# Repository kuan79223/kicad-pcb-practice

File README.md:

# KiCad PCB Design Practice

Hands-on KiCad exercises covering schematic capture, component footprints, PCB layout, design-rule checks, 3D inspection, and manufacturing-file review.

> **Scope:** This repository documents learning exercises. The boards shown here have **not** been fabricated, assembled, or physically tested.

## Projects

| Project | What I practiced | Status | Details |
| --- | --- | --- | --- |
| **01 · Zener Voltage Regulator** | 12 V input / nominal 5.1 V Zener regulator; schematic, PCB routing, 3D review, DRC, Gerber/Drill inspection | PCB design exercise completed; physical verification pending | [Open project](Zener_Regulator/README.md) |
| **02 · Common-Emitter Amplifier** | 2N3904 共射極放大器、DC 偏壓、電壓增益、PCB Layout、ERC／DRC 與 Gerber 檢視 | PCB 設計完成，待實體驗證 | [Open project](CommonEmitter_Amplifier/README.md) |
| **03 · Dual-Site Power Monitoring & Fault Detection Board** | 雙通道電源監控、LTspice、TLV7031、雙層 PCB、GND Plane |理想模型模擬及 PCB 設計初版完成；實際比較器功能與實體板待驗證 | [Open project](mini-loadboard-power-monitor/README.md) |

## Project 01 · Zener Voltage Regulator

[View the full Zener Regulator design notes →](Zener_Regulator/README.md)

## Project 02 · Common-Emitter Amplifier

[View the full CommonEmitter Amplifier design notes →](CommonEmitter_Amplifier/README.md)

## Project 02 · 雙測試位置電源監控與故障偵測板

模擬兩個測試位置的供電路徑電阻差異，使用 LTspice 分析節點壓降與理想故障判斷邏輯，並在 KiCad 建立 TLV7031 比較器原理圖、雙層 PCB、測試點及背面接地銅箔平面。

模擬條件： 3.3V 供電，理想故障判斷門檻為 3.25V。

模擬結果： SITE_A 約 3.290V、SITE_B 約 3.203V，理想故障觸發臨界路徑電阻約 5.077Ω。

工程交付： LTspice 模擬、KiCad 原理圖與 PCB、ERC／DRC、BOM、Gerber 及 Drill 資料。

驗證限制： 尚未使用實際 TLV7031 SPICE 模型或實體量測驗證比較器切換門檻。

[View the full CommonEmitter Amplifier design notes →](mini-loadboard-power-monitor/README.md)

---

*Each exercise has its own README with the circuit, design images, checks, and limitations. New projects will be added to the table above.*

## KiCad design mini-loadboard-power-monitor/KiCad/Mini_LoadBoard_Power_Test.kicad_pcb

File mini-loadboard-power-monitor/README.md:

# 雙測試位置電源監控與故障偵測板

**Dual-Site Power Monitoring & Fault Detection Board**

> 專案狀態：已完成 LTspice 理想模型驗證、KiCad 原理圖、PCB 佈線及製造資料輸出；**尚未進行實體打樣、比較器實際模型驗證或電氣量測**。

## 1. 專案目的

以簡化的雙測試位置（Site A／Site B）電源路徑作為練習案例，觀察不同路徑電阻造成的電壓降，並建立低電壓故障判斷邏輯。進一步使用 KiCad 將理想判斷概念轉換為含比較器、參考電壓、測試點與雙層 PCB 的設計初版，練習從模擬、原理圖、封裝配置、PCB 佈線到製造資料整理的工程流程。

本專案是**教學與作品集用途的簡化測試電路**，不是可直接使用的商用半導體 Load Board／BIB。

## 2. 開發工具與設計內容

| 類別 | 工具／內容 |
|---|---|
| 直流及參數掃描 | LTspice（`.op`、`.step`、Behavioral Voltage Source） |
| 原理圖與 PCB | KiCad 10.0 |
| 設計架構 | 3.3 V 供電、雙 Site 負載、兩顆 TLV7031DBV 比較器 |
| PCB | 雙層板，F.Cu 走線、B.Cu GND 銅箔區、接地 Via |
| 輸出資料 | ERC／DRC、Gerber、Excellon Drill、BOM CSV、3D 檢視 |

## 3. LTspice：雙通道直流分析

理想電源為 3.3 V；兩個 Site 均使用 330 Ω 負載，路徑電阻則分別設為 1 Ω 與 10 Ω，用於展示供電路徑阻抗不同時的壓降差異。

| 指標 | Site A | Site B |
|---|---:|---:|
| 路徑電阻 | 1 Ω | 10 Ω |
| 負載電阻 | 330 Ω | 330 Ω |
| DC 工作點電壓 | 3.29003 V | 3.20294 V |
| 支路電流 | 9.96979 mA | 9.70588 mA |
| 3.3 V 與 Site 電壓差 | 約 9.97 mV | 約 97.06 mV |

> 證據：LTspice `.op` 模擬畫面。以上數據屬理想電路模型，並非實體量測。

## 4. LTspice：理想故障判斷與門檻掃描

使用行為電壓源（Behavioral Voltage Source）描述理想低電壓故障判斷：

```text
V=if(V(SITE_A)<3.25,3.3,0)
V=if(V(SITE_B)<3.25,3.3,0)
```

當監控電壓低於 3.25 V 時，理想模型輸出 3.3 V（故障）；否則輸出 0 V（正常）。

| 監控位置 | DC 電壓 | 理想 Fault 輸出 | 判定 |
|---|---:|---:|---|
| SITE_A | 3.29003 V | 0 V | 正常 |
| SITE_B | 3.20294 V | 3.3 V | 故障 |

為了找出故障觸發條件，將 Site B 的路徑電阻設定為參數 `RPATH_B`，以 0.1 Ω 間隔從 1 Ω 掃描至 10 Ω。

理想分壓模型：

$$
V_{SITE\_B}=3.3\times\frac{330}{RPATH_B+330}
$$

當 `V(SITE_B) = 3.25 V` 時，理論臨界路徑電阻約為 **5.077 Ω**。以 0.1 Ω 掃描時，首次觀察到理想故障輸出跳升的掃描點約為 **5.1 Ω**。曲線的橫軸是電阻參數，**不是時間**。

> 重要限制：上述 `if()` 僅用來確認理想判斷邏輯；沒有模擬 TLV7031 的實際偏移電壓、內建遲滯、輸入範圍、輸出負載或動態切換特性。

## 5. KiCad：實際元件原理圖

在 KiCad 原理圖中使用兩顆 TLV7031DBV 作為電壓比較器，並以 R1 = 1 kΩ、R2 = 65 kΩ 建立共用參考電壓。在理想 3.3 V 供電及標稱電阻值下：

$$
V_{REF}=3.3\times\frac{65k}{1k+65k}=3.25\,V
$$

比較器以 `VREF` 接正相輸入、各 Site 接反相輸入，預期在 Site 電壓低於參考門檻時使 `FAULT` 輸出轉為高電位。另配置 100 nF 去耦電容、J1 供電接頭及 TP1～TP5 測試焊墊。

| 測試點 | 網路 | 功能 |
|---|---|---|
| TP1 | FAULT_A | Site A 故障輸出 |
| TP2 | FAULT_B | Site B 故障輸出 |
| TP3 | SITE_A | Site A 監控電壓 |
| TP4 | SITE_B | Site B 監控電壓 |
| TP5 | VREF | 參考電壓 |

**注意**：LTspice 與 KiCad 的電阻參考編號各自獨立，請以相對應原理圖與 BOM 為準；不得直接以編號相同視為同一顆實體電阻。KiCad 的參考電壓是取自同一組 3.3 V 電源的分壓器，無法提供獨立於供電變化的精密欠壓基準。

## 6. PCB Layout、接地設計與 3D

PCB 採雙層設計：正面 F.Cu 配置電源與訊號走線；背面 B.Cu 設置 GND 銅箔區，並透過接地 Via 連接正面 SMD 的 GND 焊墊。設計時優先考慮比較器附近的去耦、測試點可接近性與雙 Site 分區。

以上為 PCB 編輯器與 3D 模型呈現的**預期組裝外觀**，並非已製作完成的實體電路板。

## 7. 設計規則檢查與製造資料

最終截圖顯示：**0 個 DRC 違規、0 個未連接項目、0 個原理圖一致性問題**。畫面仍顯示有一類未啟用的檢查（調諧設定槽走線），因此應表述為「已啟用規則檢查通過」，而非所有可能的檢驗均已完成。

專案檔案：

- [LTspice 原始檔](LTspice/Mini_LoadBoard_Power_Test.asc)
- [KiCad 專案](KiCad/Mini_LoadBoard_Power_Test.kicad_pro)
- [KiCad 原理圖](KiCad/Mini_LoadBoard_Power_Test.kicad_sch)
- [KiCad PCB](KiCad/Mini_LoadBoard_Power_Test.kicad_pcb)
- [BOM 物料清單（CSV）](docs/Mini_LoadBoard_Power_Test.csv)
- [Gerber 製造圖形檔](fab/gerber/)
- [PTH 鑽孔檔（Excellon）](fab/Mini_LoadBoard_Power_Test-PTH.drl)
- [PTH 鑽孔圖（PDF）](fab/Mini_LoadBoard_Power_Test-PTH-drl_map.pdf)

BOM 為設計元件表，包含 Reference、Value、Footprint 及 Qty；尚未全面確認製造商料號及採購替代料。Gerber／Drill 的輸出不代表已送板生產。

## 8. 已完成與待驗證項目

| 項目 | 狀態 |
|---|---|
| LTspice 理想 DC 模型與壓降分析 | 已完成 |
| LTspice 理想故障邏輯與參數掃描 | 已完成 |
| KiCad 原理圖與初版 PCB Layout | 已完成 |
| 已啟用 ERC／DRC 規則檢查 | 已通過 |
| Gerber、Drill、BOM 輸出 | 已完成整理 |
| TLV7031 實際 SPICE 模型與門檻容差 | **尚未驗證** |
| 電源變動、電阻公差、雜訊與遲滯 | **尚未驗證** |
| 完整料號、PCB 製造條件與組裝相容性 | **送板前待確認** |
| 實體 PCB 打樣與量測 | **尚未執行** |

## 9. 專案收穫

本專案練習將**問題定義 → 理想模型 → 參數掃描 → 元件原理圖 → PCB 走線與接地 → 設計規則檢查 → 製造資料輸出**串連成可追溯的工程過程。後續若製作實體電路板，將以測試點電壓、故障切換門檻、電源誤差及比較器輸出為量測重點，並將實測結果與理想模型進行比較。

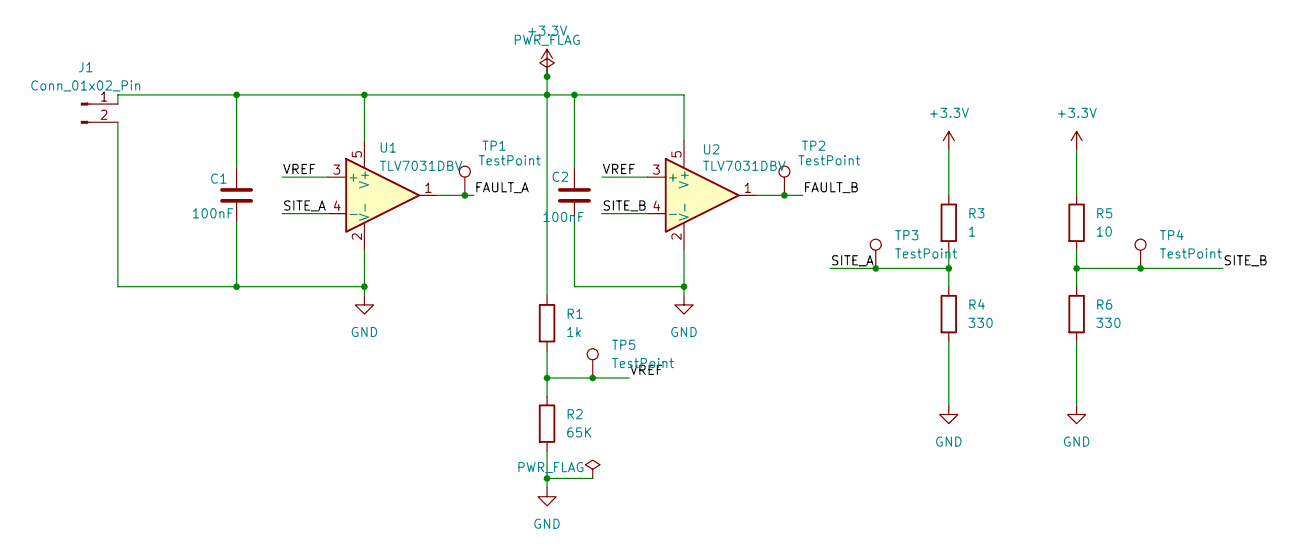
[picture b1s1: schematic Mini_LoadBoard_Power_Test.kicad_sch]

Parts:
C1, C2: 100nF; C_0805_2012Metric
J1: Conn_01x02_Pin; PinHeader_1x02_P2.54mm_Vertical
R1: 1k; R_0805_2012Metric
R2: 65K; R_0805_2012Metric
R3: 1; R_0805_2012Metric
R4, R6: 330; R_0805_2012Metric
R5: 10; R_0805_2012Metric
TP1, TP2, TP3, TP4, TP5: TestPoint; TestPoint_Pad_D1.5mm
U1, U2: TLV7031DBV; SOT-23-5

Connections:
+3.3V: C1.1, C2.1, J1.1, R1.1, R3.1, R5.1, U1.5 (V+), U2.5 (V+)
/FAULT_A: TP1.1 (1_1), U1.1
/FAULT_B: TP2.1 (1_1), U2.1
/SITE_A: R3.2, R4.1, TP3.1 (1_1), U1.4 (-)
/SITE_B: R5.2, R6.1, TP4.1 (1_1), U2.4 (-)
/VREF: R1.2, R2.1, TP5.1 (1_1), U1.3 (+), U2.3 (+)
GND: C1.2, C2.2, J1.2, R2.2, R4.2, R6.2, U1.2 (V-), U2.2 (V-)

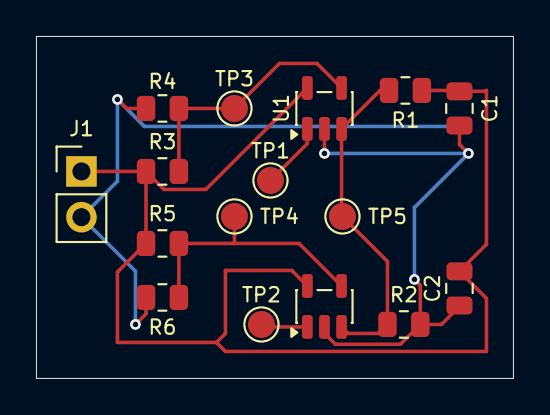
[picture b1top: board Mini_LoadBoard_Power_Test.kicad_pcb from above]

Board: 2 copper layers, 26.5 x 19.0 mm, 16 parts (0 on the bottom side), 7 nets.

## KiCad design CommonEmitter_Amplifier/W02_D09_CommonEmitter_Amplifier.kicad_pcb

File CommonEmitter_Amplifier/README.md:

[← 返回專案列表](../README.md)

# Project 02 · 2N3904 共射極放大器

**實驗目標：** 使用 KiCad 完成 2N3904 共射極放大器（Common-Emitter Amplifier）的原理圖、元件封裝配置、PCB 佈線、ERC／DRC 驗證及 Gerber 製造檔輸出。

> **學習實作專案。** 本電路已完成 LTspice 模擬及 KiCad PCB 設計，但尚未進行實體製板、焊接與量測，因此模擬結果不代表實際硬體性能。

## 1. 電路設計（Circuit Design）

| 項目 | 設計配置 |
|---|---|
| 設計軟體 | KiCad |
| 電源輸入 | DC 12 V，J1 |
| 電晶體 Q1 | 2N3904（NPN） |
| R1 / R2 | 47 kΩ / 10 kΩ，基極偏壓 |
| R3（RC） | 4.7 kΩ，集極電阻 |
| R4（RE） | 1 kΩ，射極電阻 |
| R5（RL） | 10 kΩ，輸出負載 |
| C1 / C2 | 10 µF，輸入／輸出耦合電容 |
| J1 / J2 / J3 | 電源／訊號輸入／訊號輸出 |

**電路原理：** 使用 R1、R2 建立基極分壓偏壓，使 2N3904 工作於順向主動區；透過集極電阻產生電壓放大，並利用 C1、C2 隔離直流偏壓。輸出訊號相對輸入約有 180° 相位反轉。

LTspice 模擬於約 1 kHz 時得到 9.896 dB 電壓增益與 −179.83° 相位差。

## 2. PCB 佈局與 3D 檢視（PCB Layout & 3D）

本專案採用 THT 插件式元件，包含 TO-92 電晶體、軸向電阻、徑向電解電容及外部連接端子。

已完成元件配置、銅箔佈線、電路板外框及正面絲印設計。

**PCB Layout 與絲印**

電源、訊號輸入與輸出分別透過 J1、J2、J3 連接，並標示 +12V、GND、IN、OUT，方便後續焊接及量測。

**3D 檢視**

尚未收錄 3D 截圖，待完成檢視後補上。

## 3. 設計規則檢查（DRC）

| 檢查項目 | 結果 |
|---|---|
| ERC 違規 | 0 |
| DRC 違規 | 0 |
| 未連接項目 | 0 |
| 原理圖與 PCB 一致性違規 | 0 |
| 忽略的 DRC 測試類型 | 5 |

**檢查結果：** 目前啟用的 ERC／DRC 規則均未發現違規。五類忽略測試仍須在正式製造前確認。

## 4. Gerber 與鑽孔檔檢視（Gerber & Drill）

已透過 KiCad Gerber Viewer 檢視銅箔、阻焊、正面絲印及 Edge.Cuts 板框等六個 Gerber 圖層。

Excellon 鑽孔檔（.drl）仍需另外確認。

本 Repository 以設計學習紀錄為主，暫不收錄製造檔案，也尚未委託 PCB 製造。

## 5. KiCad 原始設計檔案（Source Files）

- [KiCad 專案設定（.kicad_pro）](W02_D09_CommonEmitter_Amplifier.kicad_pro)
- [電路原理圖（.kicad_sch）](W02_D09_CommonEmitter_Amplifier.kicad_sch)
- [PCB Layout（.kicad_pcb）](W02_D09_CommonEmitter_Amplifier.kicad_pcb)

可使用 KiCad 開啟專案，檢視原理圖、元件封裝、PCB 佈線及設計規則。

## 6. 設計限制與後續驗證（Limitations）

- **尚未實體驗證：** 未進行 PCB 製板、焊接及電路量測。
- **元件規格：** 實作前須確認 2N3904 腳位、電解電容極性、封裝尺寸及額定規格。
- **電路性能：** LTspice 模擬結果仍須透過示波器及函數產生器進行實測驗證。
- **製造確認：** 正式送廠前需完成鑽孔檔、忽略規則及製造規格檢查。

---

[← 返回專案列表](../README.md)

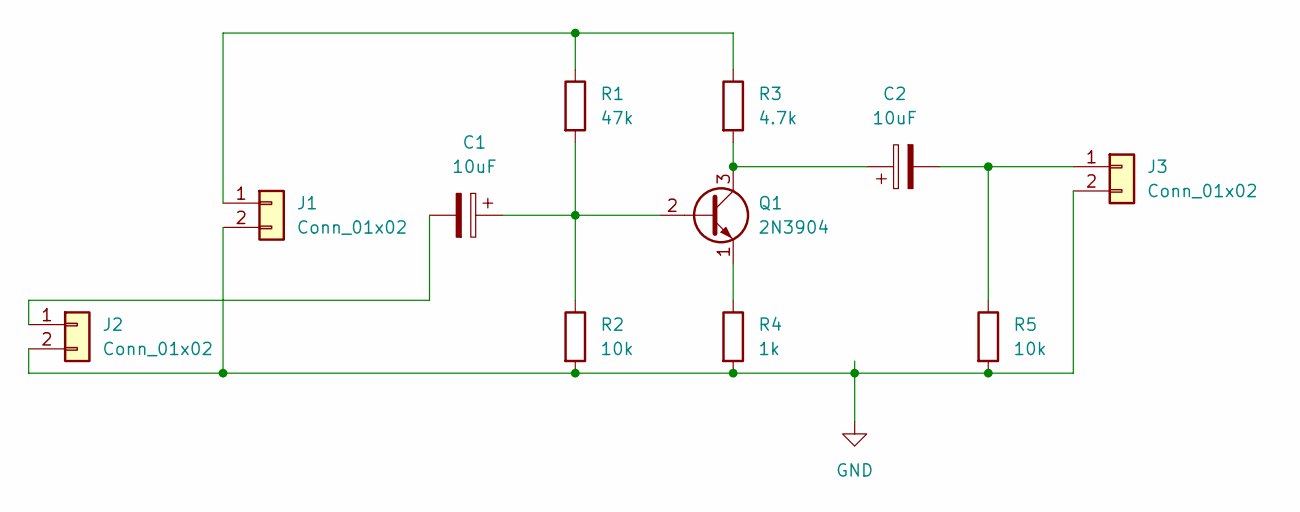
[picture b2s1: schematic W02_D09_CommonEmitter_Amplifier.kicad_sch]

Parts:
C1, C2: 10uF; CP_Radial_D5.0mm_P2.00mm
J1: Conn_01x02; TerminalBlock_MaiXu_MX126-5.0-02P_1x02_P5.00mm
J2, J3: Conn_01x02; PinHeader_1x02_P2.54mm_Vertical
Q1: 2N3904; TO-92_Inline
R1: 47k; R_Axial_DIN0207_L6.3mm_D2.5mm_P7.62mm_Horizontal
R2, R5: 10k; R_Axial_DIN0207_L6.3mm_D2.5mm_P7.62mm_Horizontal
R3: 4.7k; R_Axial_DIN0207_L6.3mm_D2.5mm_P7.62mm_Horizontal
R4: 1k; R_Axial_DIN0207_L6.3mm_D2.5mm_P7.62mm_Horizontal

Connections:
GND: J1.2, J2.2, J3.2, R2.2, R4.2, R5.2
unnamed: J1.1, R1.1, R3.1
unnamed: C1.2, J2.1
unnamed: C2.2, J3.1, R5.1
unnamed: C1.1, Q1.2 (B), R1.2, R2.1
unnamed: C2.1, Q1.3 (C), R3.2
unnamed: Q1.1 (E), R4.1

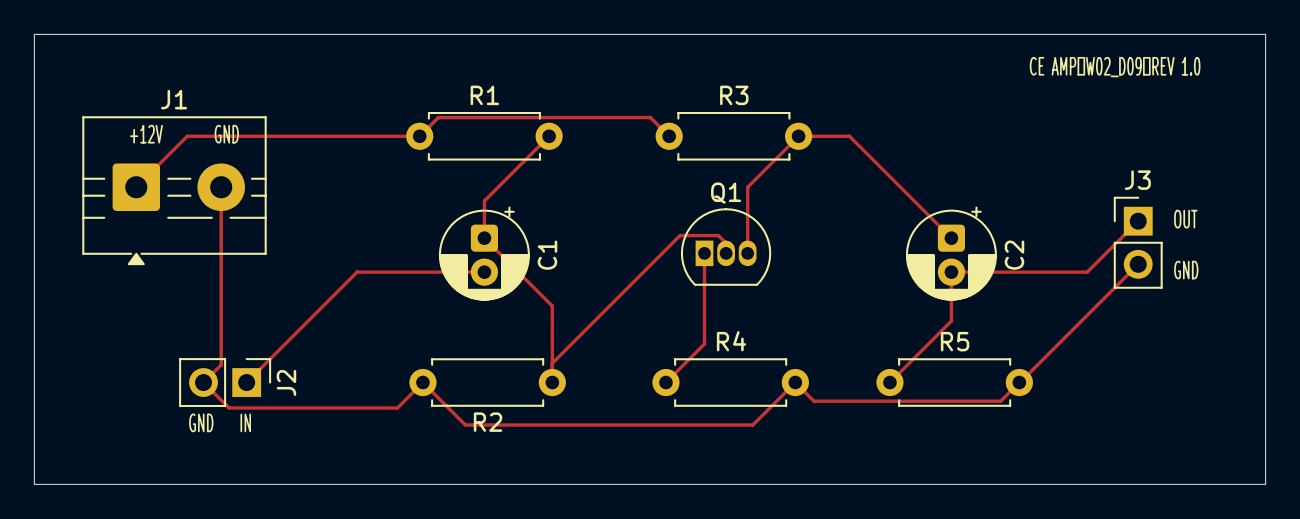
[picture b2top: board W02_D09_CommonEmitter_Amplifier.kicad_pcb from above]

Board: 2 copper layers, 72.5 x 26.5 mm, 11 parts (0 on the bottom side), 7 nets.

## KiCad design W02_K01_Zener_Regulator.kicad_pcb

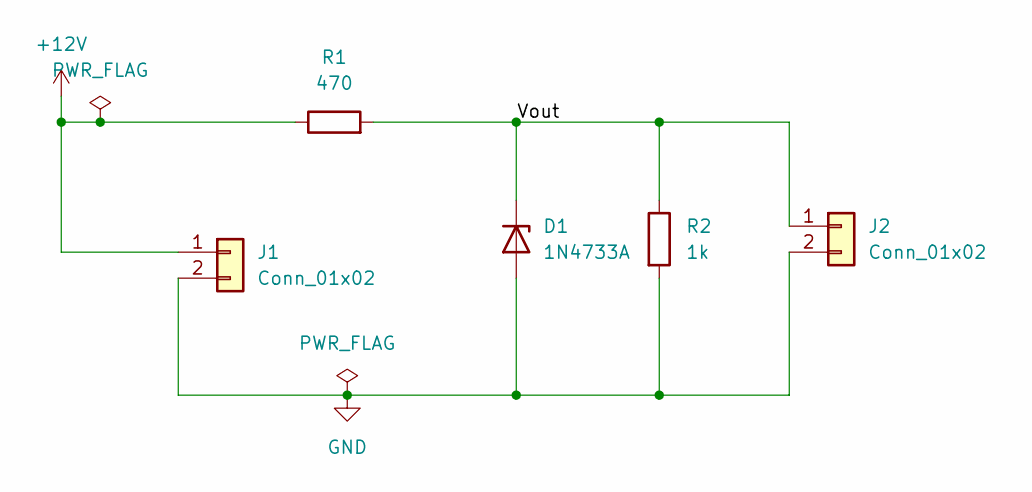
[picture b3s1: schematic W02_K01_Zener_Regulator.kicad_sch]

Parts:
D1: 1N4733A; D_DO-41_SOD81_P10.16mm_Horizontal
J1, J2: Conn_01x02; TerminalBlock_Phoenix_MKDS-1,5-2-5.08_1x02_P5.08mm_Horizont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
R1: 470; R_Axial_DIN0309_L9.0mm_D3.2mm_P12.70mm_Horizontal
R2: 1k; R_Axial_DIN0207_L6.3mm_D2.5mm_P7.62mm_Horizontal

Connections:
+12V: J1.1, R1.1
/Vout: D1.1 (K), J2.1, R1.2, R2.1
GND: D1.2 (A), J1.2, J2.2, R2.2

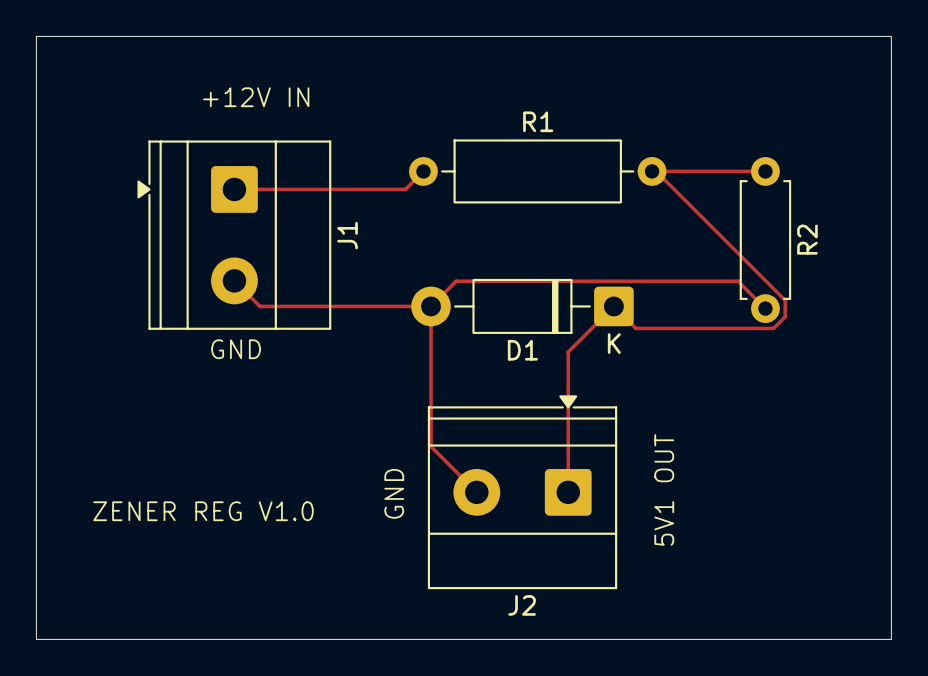
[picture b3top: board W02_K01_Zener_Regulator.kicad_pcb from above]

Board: 2 copper layers, 47.5 x 33.5 mm, 5 parts (0 on the bottom side), 3 nets.
